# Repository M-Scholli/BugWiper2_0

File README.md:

## New ESP32-S3 Version

The new version of the BugWiper system is a complete redesign of the hardware and software to improve the performance, reliability and features of the system. The new design is based on the ESP32-S3 micro controller. The new design also includes a new motor with higher torque, a self locking gear and a motor encoder to measure the motor position and speed. The new design also includes a new software architecture that allows for more advanced features like programmable cable length, soft direction change of the motor at the wingtip, slow down the motor before reaching the fuselage and logging of all sensor data on an SD-card for later analysis and optimization of the system.

The BugWiper System cleans the wings in around 30 seconds as shown in this graph:

The documentation of the new version is still in progress, but you can already find some information about the hardware and software design in the following documents:
 [Documentation](./docs/doc.md)

 The user manual can be found here:
 [User Manual](./docs/user_manuel.md)

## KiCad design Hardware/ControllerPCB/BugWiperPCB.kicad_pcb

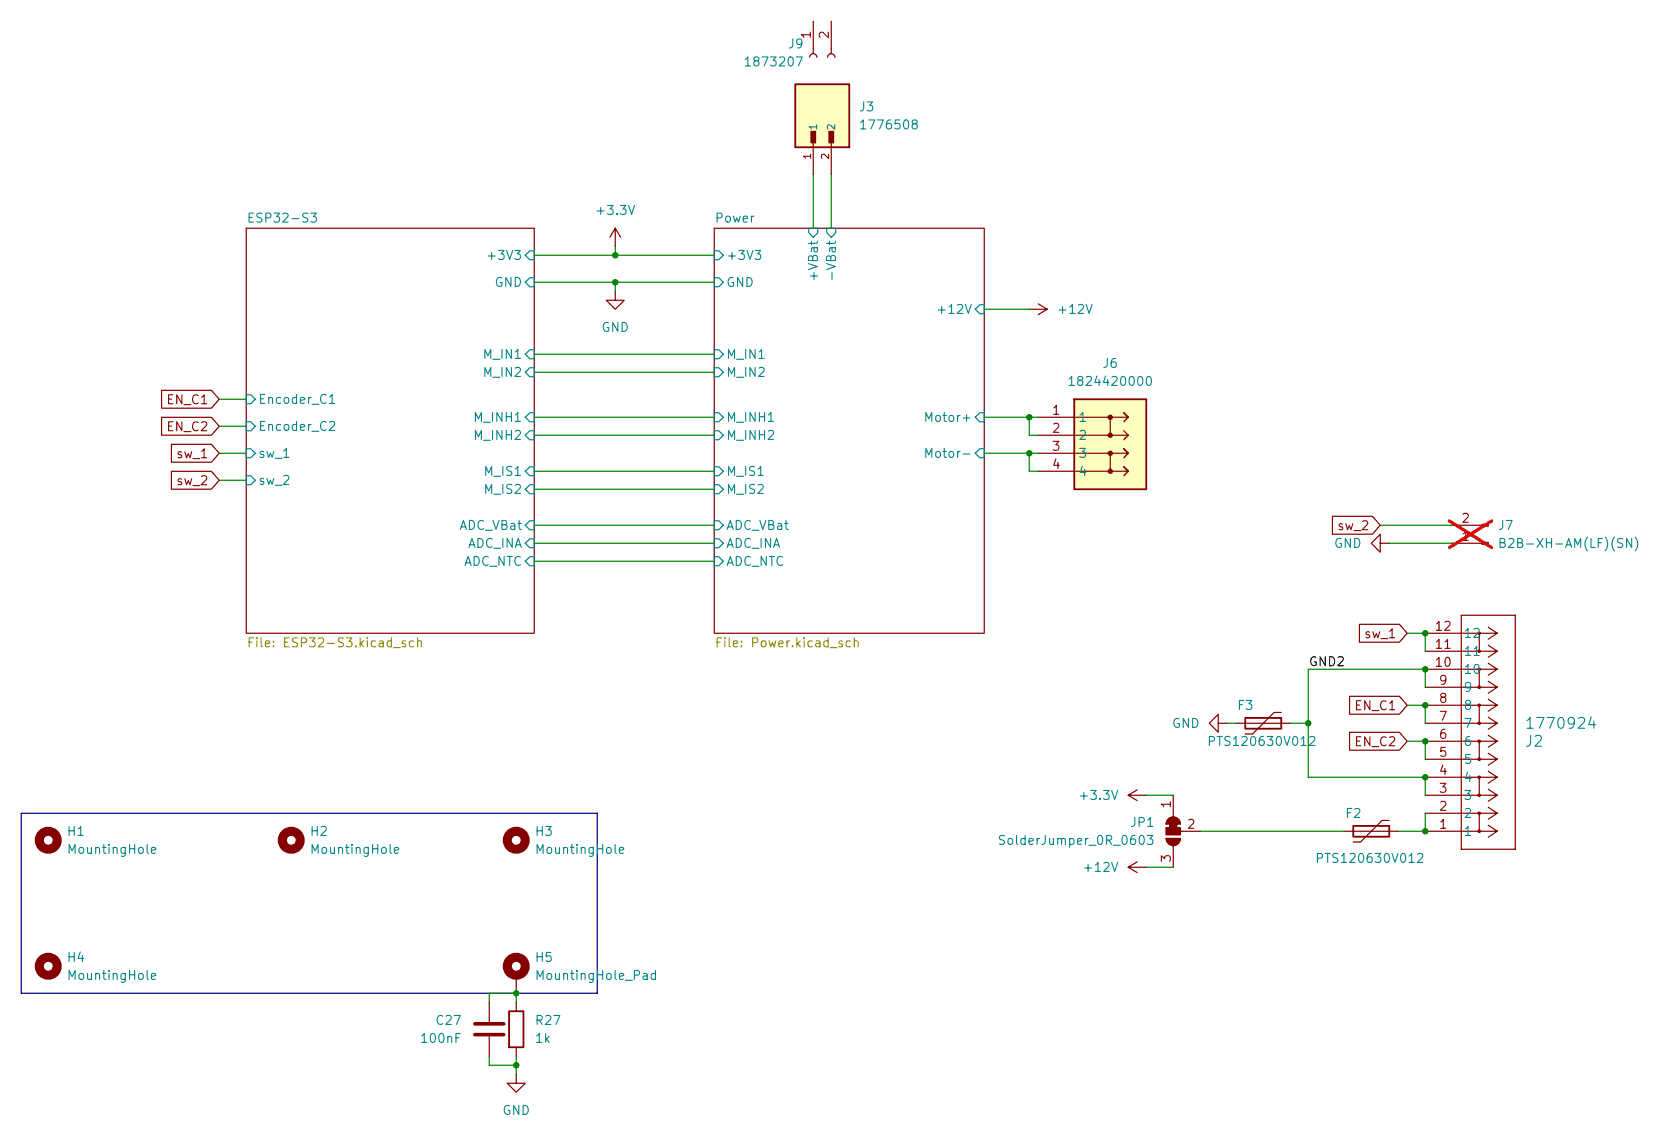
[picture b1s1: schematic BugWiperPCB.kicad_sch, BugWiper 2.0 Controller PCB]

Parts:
C27: 100nF; C_0603_1608Metric; Manufacturer_Part_Number CL10B104KB8NNNC; Mouser Part Number 187-CL10B104KB8NNNC
F2, F3: PTS120630V012; R_1206_3216Metric; Manufacturer_Part_Number PTS120630V012; Mouser Part Number 504-PTS120630V012
H1, H2, H3, H4: MountingHole; MountingHole_3.2mm_M3_DIN965_Pad
H5: MountingHole_Pad; MountingHole_3.2mm_M3_DIN965_Pad_TopBottom
J2: 1770924; CONN_1814537; Manufacturer_Part_Number 1770924; Mouser Part Number 651-1770924
J3: 1776508; PHOENIX_1776508; Manufacturer_Part_Number 1776508; Mouser Part Number 651-1776508
J6: 1824420000; SHDR4W80P700X350_2X2_770X1400X850P; Mouser Part Number 470-1824420000
J7: B2B-XH-AM(LF)(SN); JST_XH_B2B-XH-AM_1x02_P2.50mm_Vertical; Manufacturer_Part_Number B2B-XH-AM(LF)(SN); Mouser Part Number 306-B2B-XH-AMLFSNP; not fitted
J9: 1873207; Manufacturer_Part_Number 1873207; Mouser Part Number 651-1873207
JP1: SolderJumper_0R_0603; SolderJumper_R_SMD_0603; Manufacturer_Part_Number RC0603FR-070RL; Mouser Part Number 603-RC0603FR-070RL
R27: 1k; R_0603_1608Metric; Manufacturer_Part_Number RC0603FR-071KL; Mouser Part Number 603-RC0603FR-071KL

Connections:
+3.3V: JP1.1 (A); also elsewhere on the board
+12V: JP1.3 (B); also elsewhere on the board
/GND2: F3.1, J2.3, J2.4, J2.9, J2.10
/Power/+VBat: J3.1; also elsewhere on the board
/Power/Motor+: J6.1, J6.2; also elsewhere on the board
/Power/Motor-: J6.3, J6.4; also elsewhere on the board
EN_C1: J2.7, J2.8; also elsewhere on the board
EN_C2: J2.5, J2.6; also elsewhere on the board
GND: C27.2, F3.2, J3.2, J7.1, R27.2; also elsewhere on the board
unnamed: C27.1, H5.1, R27.1
unnamed: F2.1, J2.1, J2.2
unnamed: F2.2, JP1.2 (C)
sw_1: J2.11, J2.12; also elsewhere on the board
sw_2: J7.2; also elsewhere on the board

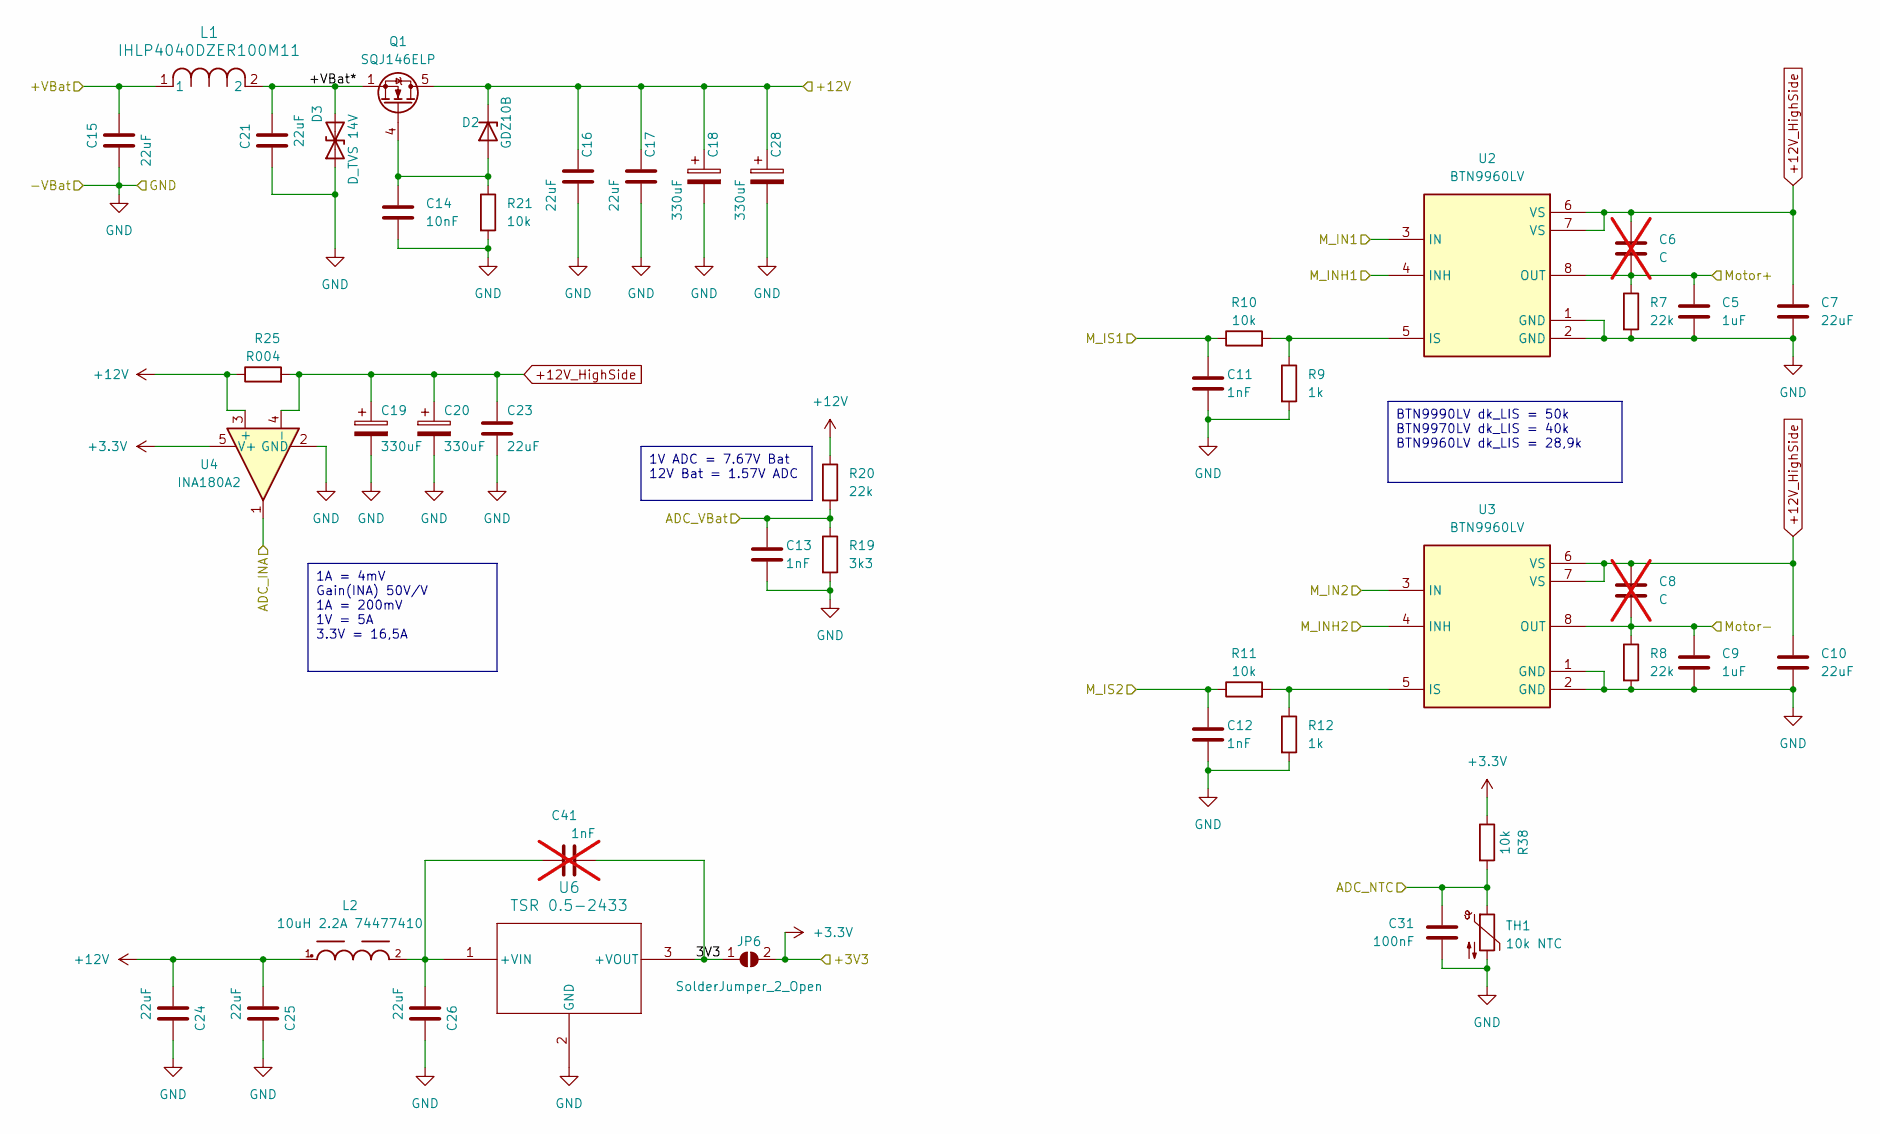
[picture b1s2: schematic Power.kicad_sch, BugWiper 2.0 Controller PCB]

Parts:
C5, C9: 1uF; C_0805_2012Metric; Manufacturer_Part_Number CL21B105MBFNNNE; Mouser Part Number 187-CL21B105MBFNNNE
C6, C8: C; C_0603_1608Metric; not fitted
C7, C10, C24, C25, C26: 22uF; C_1206_3216Metric; Manufacturer_Part_Number CL31A226KAHNNNE; Mouser Part Number 187-CL31A226KAHNNNE
C11, C12, C13: 1nF; C_0603_1608Metric; Manufacturer_Part_Number KAM15AR71H102KM; Mouser Part Number 581-KAM15AR71H102KM
C14: 10nF; C_0603_1608Metric; Manufacturer_Part_Number CL10B103KB8NFNC; Mouser Part Number 187-CL10B103KB8NFNC
C15, C16, C17, C21, C23: 22uF; C_1210_3225Metric; Manufacturer_Part_Number CL31A226KAHNNNE; Mouser Part Number 187-CL31A226KAHNNNE
C18, C19, C20, C28: 330uF; CP_Elec_8x10.5; Manufacturer_Part_Number UWT1E331MNL1GS; Mouser Part Number 647-UWT1E331MNL1S
C31: 100nF; C_0603_1608Metric; Manufacturer_Part_Number CL10B104KB8NNNC; Mouser Part Number 187-CL10B104KB8NNNC
C41: 1nF; C_0805_2012Metric_Pad1.18x1.45mm_HandSolder; not fitted
D2: GDZ10B; D_SOD-323_HandSoldering; Manufacturer_Part_Number GDZ10B-E3-08; Mouser Part Number 78-GDZ10B-E3-08
D3: D_TVS 14V; D_SMB; Manufacturer_Part_Number SMBJ14CA-13-F; Mouser Part Number 621-SMBJ14CA-13-F
JP6: SolderJumper_2_Open; SolderJumper-2_P1.3mm_Open_TrianglePad1.0x1.5mm
L1: IHLP4040DZER100M11; IND_IHLP-4040DZ_VIS; Manufacturer_Part_Number IHLP4040DZER100M11; Mouser Part Number 70-IHLP4040DZER100M1
L2: 10uH 2.2A 74477410; WE-PD2_5848; Manufacturer_Part_Number 74477410; Mouser Part Number 710-74477410
Q1: SQJ146ELP; PowerPAK_SO-8L_3_VIS; Manufacturer_Part_Number SQJ146ELP-T1_GE3; Mouser Part Number 78-SQJ146ELP-T1_GE3
R7, R8, R20: 22k; R_0603_1608Metric; Manufacturer_Part_Number AC0603FR-1022KL; Mouser Part Number 603-AC0603FR-1022KL
R9, R12: 1k; R_0603_1608Metric; Manufacturer_Part_Number RC0603FR-071KL; Mouser Part Number 603-RC0603FR-071KL
R10, R11, R21, R38: 10k; R_0603_1608Metric; Manufacturer_Part_Number RC0603FR-1010KL; Mouser Part Number 603-RC0603FR-1010KL
R19: 3k3; R_0603_1608Metric; Manufacturer_Part_Number CR0603-FX-3301ELF; Mouser Part Number 652-CR0603-FX3301ELF
R25: R004; R_1210_3225Metric; Manufacturer_Part_Number LRMAM1206-R004FT5; Mouser Part Number 756-LRMAM1206R004FT5
TH1: 10k NTC; R_0603_1608Metric; Manufacturer_Part_Number NCU18XH103E60RB; Mouser Part Number 81-NCU18XH103E60RB
U2, U3: BTN9960LV; IFX-PG-HSOF-7-1-V; Manufacturer_Part_Number BTN9960LVAUMA1; Mouser Part Number 726-BTN9960LVAUMA1
U4: INA180A2; SOT-23-5; Manufacturer_Part_Number INA180A2IDBVT; Mouser Part Number 595-INA180A2IDBVT
U6: TSR 0.5-2433; TSR0P5_TRP; Manufacturer_Part_Number R-78E3.3-0.5; Mouser Part Number 919-R-78E3.3-0.5

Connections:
+3.3V: JP6.2 (B), R38.1, U4.5 (V+); also elsewhere on the board
+12V: C16.1, C17.1, C18.1, C24.2, C25.2, C28.1, D2.1 (K), L2.1, Q1.5 (D), R20.1, R25.1, U4.3 (+); also elsewhere on the board
+12V_HighSide: C6.1, C7.1, C8.1, C10.1, C19.1, C20.1, C23.1, R25.2, U2.6 (VS), U2.7 (VS), U3.6 (VS), U3.7 (VS), U4.4 (-)
/ESP32-S3/ADC_INA: U4.1; also elsewhere on the board
/ESP32-S3/ADC_NTC: C31.1, R38.2, TH1.1; also elsewhere on the board
/ESP32-S3/ADC_VBat: C13.1, R19.1, R20.2; also elsewhere on the board
/ESP32-S3/M_IN1: U2.3 (IN); also elsewhere on the board
/ESP32-S3/M_IN2: U3.3 (IN); also elsewhere on the board
/ESP32-S3/M_INH1: U2.4 (INH); also elsewhere on the board
/ESP32-S3/M_INH2: U3.4 (INH); also elsewhere on the board
/ESP32-S3/M_IS1: C11.1, R10.1; also elsewhere on the board
/ESP32-S3/M_IS2: C12.1, R11.1; also elsewhere on the board
/Power/3V3: C41.2, JP6.1 (A), U6.3 (+VOUT)
/Power/+VBat: C15.1, L1.1; also elsewhere on the board
/Power/+VBat*: C21.2, D3.2 (A2), L1.2, Q1.1 (S), Q1.2 (S), Q1.3 (S)
/Power/Motor+: C5.1, C6.2, R7.1, U2.8 (OUT); also elsewhere on the board
/Power/Motor-: C8.2, C9.1, R8.1, U3.8 (OUT); also elsewhere on the board
GND: C5.2, C7.2, C9.2, C10.2, C11.2, C12.2, C13.2, C14.2, C15.2, C16.2, C17.2, C18.2, C19.2, C20.2, C21.1, C23.2, C24.1, C25.1, C26.1, C28.2, C31.2, D3.1 (A1), R7.2, R8.2, R9.2, R12.2, R19.2, R21.2, TH1.2, U2.1 (GND), U2.2 (GND), U3.1 (GND), U3.2 (GND), U4.2 (GND), U6.2 (GND); also elsewhere on the board
unnamed: C14.1, D2.2 (A), Q1.4 (G), R21.1
unnamed: R9.1, R10.2, U2.5 (IS)
unnamed: R11.2, R12.1, U3.5 (IS)
unnamed: C26.2, C41.1, L2.2, U6.1 (+VIN)

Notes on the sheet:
1A = 4mV Gain(INA) 50V/V 1A = 200mV 1V = 5A 3.3V = 16,5A
1V ADC = 7.67V Bat 12V Bat = 1.57V ADC
BTN9990LV dk_LIS = 50k BTN9970LV dk_LIS = 40k BTN9960LV dk_LIS = 28,9k

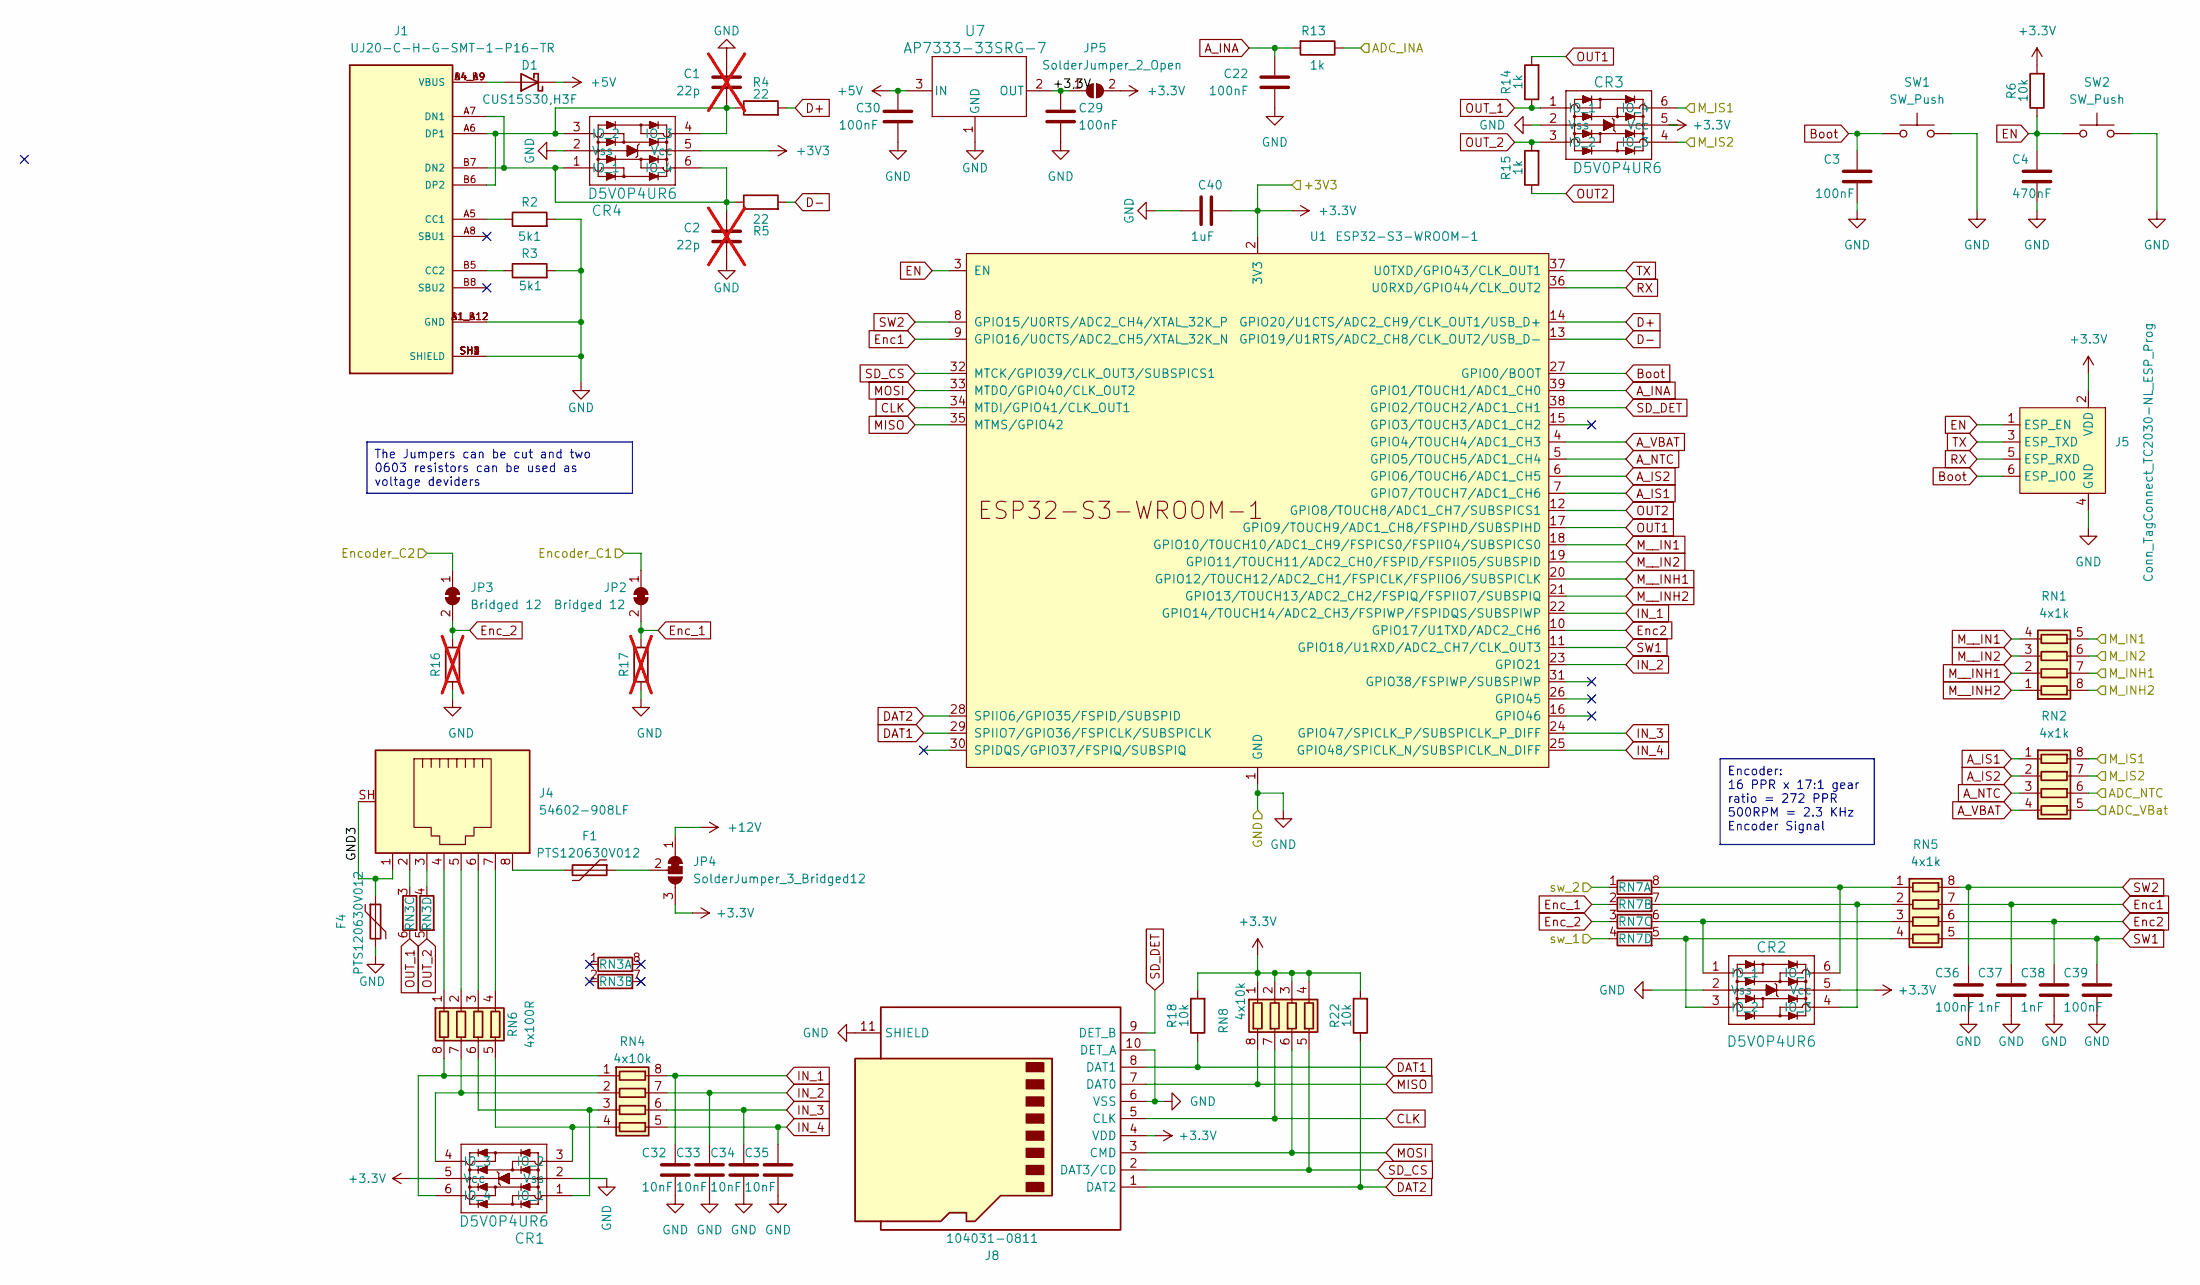
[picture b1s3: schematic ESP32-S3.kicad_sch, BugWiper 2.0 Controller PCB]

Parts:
C1, C2: 22p; C_0603_1608Metric; not fitted
C3, C22, C29, C30, C39: 100nF; C_0603_1608Metric; Manufacturer_Part_Number CL10B104KB8NNNC; Mouser Part Number 187-CL10B104KB8NNNC
C4: 470nF; C_0603_1608Metric; Manufacturer_Part_Number CL10B474KA8NFNC; Mouser Part Number 187-CL10B474KA8NFNC
C32, C33, C34, C35: 10nF; C_0603_1608Metric; Manufacturer_Part_Number CL10B103KB8NFNC; Mouser Part Number 187-CL10B103KB8NFNC
C36: 100nF; C_0603_1608Metric; Manufacturer_Part_Number CL10B103KB8NFNC; Mouser Part Number 187-CL10B103KB8NFNC
C37: 1nF; C_0603_1608Metric; Manufacturer_Part_Number CL10B103KB8NFNC; Mouser Part Number 187-CL10B103KB8NFNC
C38: 1nF; C_0603_1608Metric; Manufacturer_Part_Number CL10B104KB8NNNC; Mouser Part Number 187-CL10B104KB8NNNC
C40: 1uF; C_0805_2012Metric; Manufacturer_Part_Number CL21B105MBFNNNE; Mouser Part Number 187-CL21B105MBFNNNE
CR1, CR2, CR3, CR4: D5V0P4UR6; SOT26_DIO; Manufacturer_Part_Number D5V0P4UR6SO-7; Mouser Part Number 621-D5V0P4UR6SO-7
D1: CUS15S30,H3F; D_SOD-323_HandSoldering; Manufacturer_Part_Number CUS15S30,H3F; Mouser Part Number 757-CUS15S30H3F
F1, F4: PTS120630V012; R_1206_3216Metric; Manufacturer_Part_Number PTS120630V012; Mouser Part Number 504-PTS120630V012
J1: UJ20-C-H-G-SMT-1-P16-TR; SAMESKY_UJ20-C-H-G-SMT-1-P16-TR; Manufacturer_Part_Number UJ20-C-H-G-SMT-1-P16-TR; Mouser Part Number 179-UJ20CHGSMT1P16TR
J4: 54602-908LF; CONN8_2-908LF_AMP; Manufacturer_Part_Number 54602-908LF; Mouser Part Number 649-54602-908LF
J5: Conn_TagConnect_TC2030-NL_ESP_Prog; Tag-Connect_TC2030-IDC-NL_2x03_P1.27mm_Vertical; Mouser Price/Stock 0€
J8: 104031-0811; microSD_HC_Molex_104031-0811; Manufacturer_Part_Number 104031-0811; Mouser Part Number 538-104031-0811
JP2, JP3: Bridged 12; SolderJumper_2P_R_SMD_0603_Bridged
JP4: SolderJumper_3_Bridged12; SolderJumper_3P_R_SMD_0603_Bridged_12
JP5: SolderJumper_2_Open; SolderJumper-2_P1.3mm_Open_TrianglePad1.0x1.5mm
R2, R3: 5k1; R_0603_1608Metric; Manufacturer_Part_Number RC0603FR-105K1L; Mouser Part Number 603-RC0603FR-105K1L
R4, R5: 22; R_0603_1608Metric; Manufacturer_Part_Number CR0603-FX-22R0ELF; Mouser Part Number 652-CR0603FX-22R0ELF
R6, R18, R22: 10k; R_0603_1608Metric; Manufacturer_Part_Number RC0603FR-1010KL; Mouser Part Number 603-RC0603FR-1010KL
R13, R14, R15: 1k; R_0603_1608Metric; Manufacturer_Part_Number RC0603FR-071KL; Mouser Part Number 603-RC0603FR-071KL
R16, R17: R_0603_1608Metric; not fitted
RN1, RN2, RN5: 4x1k; RESCAV80P320X155X60-8N; Manufacturer_Part_Number CAY16-1001F4LF; Mouser Part Number 652-CAY16-1001F4LF
RN3, RN6, RN7: 4x100R; RESCAV80P320X155X60-8N; Manufacturer_Part_Number CAT16A-1000F4LF; Mouser Part Number 652-CAT16A-1000F4LF
RN4, RN8: 4x10k; RESCAV80P320X155X60-8N; Manufacturer_Part_Number CAT16A-1002F4LF; Mouser Part Number 652-CAT16A-1002F4LF
SW1, SW2: SW_Push; EVQ9P701P; Manufacturer_Part_Number EVQ-P3401P; Mouser Part Number 667-EVQP3401P
U1: ESP32-S3-WROOM-1; Manufacturer_Part_Number ESP32-S3-WROOM-1-N16R8; Mouser Part Number 356-ESP32S3WRM1N16R8
U7: AP7333-33SRG-7; SOT23R_DIO; Manufacturer_Part_Number AP7333-33SRG-7; Mouser Part Number 621-AP7333-33SRG-7

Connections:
+3.3V: C40.2, CR1.5 (Vcc), CR2.5 (Vcc), CR3.5 (Vcc), CR4.5 (Vcc), J5.2 (VDD), J8.4 (VDD), JP4.3 (B), JP5.2 (B), R6.2, R18.2, R22.2, RN8.1 (R1.1), RN8.2 (R2.1), RN8.3 (R3.1), RN8.4 (R4.1), U1.2 (3V3); also elsewhere on the board
+5V: C30.1, D1.1 (K), U7.3 (IN)
+12V: JP4.1 (A); also elsewhere on the board
/ESP32-S3/+3,3V: C29.1, JP5.1 (A), U7.2 (OUT)
/ESP32-S3/ADC_INA: R13.1; also elsewhere on the board
/ESP32-S3/ADC_NTC: RN2.6 (R3.2); also elsewhere on the board
/ESP32-S3/ADC_VBat: RN2.5 (R4.2); also elsewhere on the board
/ESP32-S3/GND3: F4.1, J4.1, J4.SH
/ESP32-S3/M_IN1: RN1.5 (R4.2); also elsewhere on the board
/ESP32-S3/M_IN2: RN1.6 (R3.2); also elsewhere on the board
/ESP32-S3/M_INH1: RN1.7 (R2.2); also elsewhere on the board
/ESP32-S3/M_INH2: RN1.8 (R1.2); also elsewhere on the board
/ESP32-S3/M_IS1: CR3.6 (IO_4), RN2.8 (R1.2); also elsewhere on the board
/ESP32-S3/M_IS2: CR3.4 (IO_3), RN2.7 (R2.2); also elsewhere on the board
A_INA: C22.1, R13.2, U1.39 (GPIO1/TOUCH1/ADC1_CH0)
A_IS1: RN2.1 (R1.1), U1.7 (GPIO7/TOUCH7/ADC1_CH6)
A_IS2: RN2.2 (R2.1), U1.6 (GPIO6/TOUCH6/ADC1_CH5)
A_NTC: RN2.3 (R3.1), U1.5 (GPIO5/TOUCH5/ADC1_CH4)
A_VBAT: RN2.4 (R4.1), U1.4 (GPIO4/TOUCH4/ADC1_CH3)
Boot: C3.1, J5.6 (ESP_IO0), SW1.1, U1.27 (GPIO0/BOOT)
CLK: J8.5 (CLK), RN8.7 (R2.2), U1.34 (MTDI/GPIO41/CLK_OUT1)
D+: R4.2, U1.14 (GPIO20/U1CTS/ADC2_CH9/CLK_OUT1/USB_D+)
D-: R5.2, U1.13 (GPIO19/U1RTS/ADC2_CH8/CLK_OUT2/USB_D-)
DAT1: J8.8 (DAT1), R18.1, U1.29 (SPIIO7/GPIO36/FSPICLK/SUBSPICLK)
DAT2: J8.1 (DAT2), R22.1, U1.28 (SPIIO6/GPIO35/FSPID/SUBSPID)
EN: C4.1, J5.1 (ESP_EN), R6.1, SW2.1, U1.3 (EN)
EN_C1: JP2.1 (A); also elsewhere on the board
EN_C2: JP3.1 (A); also elsewhere on the board
Enc1: C37.1, RN5.7 (R2.2), U1.9 (GPIO16/U0CTS/ADC2_CH5/XTAL_32K_N)
Enc2: C38.1, RN5.6 (R3.2), U1.10 (GPIO17/U1TXD/ADC2_CH6)
Enc_1: JP2.2 (A), R17.2, RN7.2 (R2.1)
Enc_2: JP3.2 (A), R16.2, RN7.3 (R3.1)
GND: C1.1, C2.2, C3.2, C4.2, C22.2, C29.2, C30.2, C32.2, C33.2, C34.2, C35.2, C36.2, C37.2, C38.2, C39.2, C40.1, CR1.2 (Vss), CR2.2 (Vss), CR3.2 (Vss), CR4.2 (Vss), F4.2, J1.A1_B12 (GND), J1.B1_A12 (GND), J1.SH1 (SHIELD), J1.SH2 (SHIELD), J1.SH3 (SHIELD), J1.SH4 (SHIELD), J5.4 (GND), J8.6 (VSS), J8.10 (DET_A), J8.11 (SHIELD), R2.2, R3.2, R16.1, R17.1, SW1.2, SW2.2, U1.1 (GND), U1.40 (GND), U1.41 (GND), U7.1 (GND); also elsewhere on the board
IN_1: C32.1, RN4.8 (R1.2), U1.22 (GPIO14/TOUCH14/ADC2_CH3/FSPIWP/FSPIDQS/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)
IN_2: C33.1, RN4.7 (R2.2), U1.23 (GPIO21)
IN_3: C34.1, RN4.6 (R3.2), U1.24 (GPIO47/SPICLK_P/SUBSPICLK_P_DIFF)
IN_4: C35.1, RN4.5 (R4.2), U1.25 (GPIO48/SPICLK_N/SUBSPICLK_N_DIFF)
MISO: J8.7 (DAT0), RN8.8 (R1.2), U1.35 (MTMS/GPIO42)
MOSI: J8.3 (CMD), RN8.6 (R3.2), U1.33 (MTDO/GPIO40/CLK_OUT2)
M__IN1: RN1.4 (R4.1), U1.18 (GPIO10/TOUCH10/ADC1_CH9/FSPICS0/FSPIIO4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)
M__IN2: RN1.3 (R3.1), U1.19 (GPIO11/TOUCH11/ADC2_CH0/FSPID/FSPIIO5/S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)
M__INH1: RN1.2 (R2.1), U1.20 (GPIO12/TOUCH12/ADC2_CH1/FSPICLK/FSPIIO6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)
M__INH2: RN1.1 (R1.1), U1.21 (GPIO13/TOUCH13/ADC2_CH2/FSPIQ/FSPIIO7/S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)
unnamed: CR1.1 (IO_1), RN4.3 (R3.1), RN6.6 (R3.2)
unnamed: CR1.3 (IO_2), RN4.4 (R4.1), RN6.5 (R4.2)
unnamed: CR1.4 (IO_3), RN4.2 (R2.1), RN6.7 (R2.2)
unnamed: CR1.6 (IO_4), RN4.1 (R1.1), RN6.8 (R1.2)
unnamed: CR2.1 (IO_1), RN5.3 (R3.1), RN7.6 (R3.2)
unnamed: CR2.3 (IO_2), RN5.4 (R4.1), RN7.5 (R4.2)
unnamed: CR2.4 (IO_3), RN5.2 (R2.1), RN7.7 (R2.2)
unnamed: CR2.6 (IO_4), RN5.1 (R1.1), RN7.8 (R1.2)
unnamed: C2.1, CR4.1 (IO_1), CR4.6 (IO_4), J1.A7 (DN1), J1.B7 (DN2), R5.1
unnamed: C1.2, CR4.3 (IO_2), CR4.4 (IO_3), J1.A6 (DP1), J1.B6 (DP2), R4.1
unnamed: D1.2 (A), J1.A4_B9 (VBUS), J1.B4_A9 (VBUS)
unnamed: F1.2, J4.8
unnamed: J1.A5 (CC1), R2.1
unnamed: J1.B5 (CC2), R3.1
unnamed: F1.1, JP4.2 (C)
unnamed: J4.2, RN3.3 (R3.1)
unnamed: J4.3, RN3.4 (R4.1)
unnamed: J4.4, RN6.1 (R1.1)
unnamed: J4.5, RN6.2 (R2.1)
unnamed: J4.6, RN6.3 (R3.1)
unnamed: J4.7, RN6.4 (R4.1)
OUT1: R14.2, U1.17 (GPIO9/TOUCH9/ADC1_CH8/FSPIHD/SUBSPIHD)
OUT2: R15.1, U1.12 (GPIO8/TOUCH8/ADC1_CH7/SUBSPICS1)
OUT_1: CR3.1 (IO_1), R14.1, RN3.6 (R3.2)
OUT_2: CR3.3 (IO_2), R15.2, RN3.5 (R4.2)
RX: J5.5 (ESP_RXD), U1.36 (U0RXD/GPIO44/CLK_OUT2)
SD_CS: J8.2 (DAT3/CD), RN8.5 (R4.2), U1.32 (MTCK/GPIO39/CLK_OUT3/SUBSPICS1)
SD_DET: J8.9 (DET_B), U1.38 (GPIO2/TOUCH2/ADC1_CH1)
SW1: C39.1, RN5.5 (R4.2), U1.11 (GPIO18/U1RXD/ADC2_CH7/CLK_OUT3)
SW2: C36.1, RN5.8 (R1.2), U1.8 (GPIO15/U0RTS/ADC2_CH4/XTAL_32K_P)
TX: J5.3 (ESP_TXD), U1.37 (U0TXD/GPIO43/CLK_OUT1)
sw_1: RN7.4 (R4.1); also elsewhere on the board
sw_2: RN7.1 (R1.1); also elsewhere on the board

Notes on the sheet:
Encoder: 16 PPR x 17:1 gear ratio = 272 PPR 500RPM = 2.3 KHz Encoder Signal
The Jumpers can be cut and two 0603 resistors can be used as voltage deviders

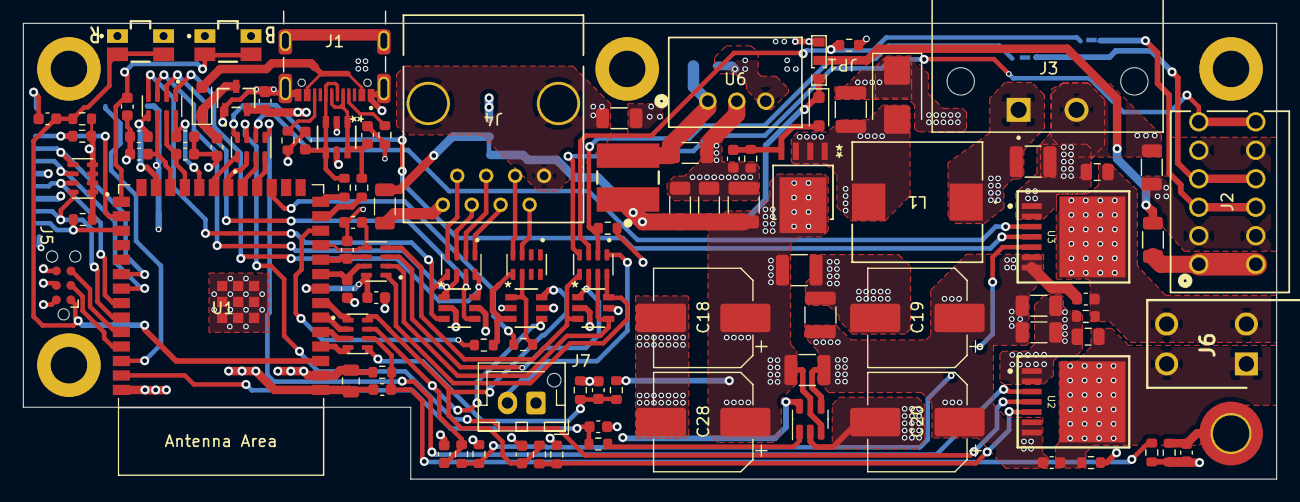
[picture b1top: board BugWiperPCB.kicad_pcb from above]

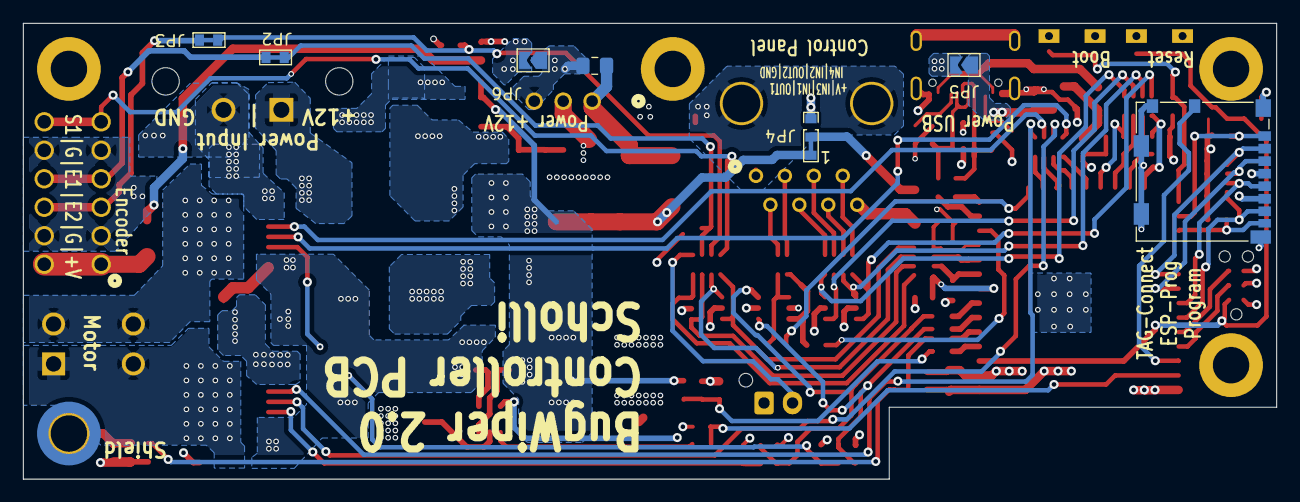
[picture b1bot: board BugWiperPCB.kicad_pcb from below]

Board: 4 copper layers, 110.0 x 40.0 mm, 115 parts (7 on the bottom side), 90 nets.

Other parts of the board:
locked: MountingHole; MountingHole_3.2mm_M3_DIN965_Pad

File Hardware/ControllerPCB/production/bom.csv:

Designator,Footprint,Quantity,Value,LCSC Part #
"C10, C24, C25, C26, C7",1206,5,22uF 25V,
"C11, C12, C13",0603,3,1nF,
"C14, C32, C33, C34, C35, C36, C37",0603,7,10nF ,
"C15, C16, C17, C21, C23",1210,5,22uF 25V,
"C18, C19, C20, C28",CP_Elec_8x10.5,4,470uF 16V,
"C22, C27, C29, C3, C30, C31, C38, C39, C4",0603,9,100nF ,
"C40, C5, C9",0805,3,1uF 50V,
"CR1, CR2, CR3, CR4",SOT26_DIO,4,D5V0P4UR6SO-7,
D1,D_SOD-323_HandSoldering,1,"CUS15S30,H3F",
D2,D_SOD-323_HandSoldering,1,D_Zener 10V,
D3,D_SMB,1,D_TVS 15V,
"F1, F2, F3, F4",1206,4,100mA Polyfuse,
"H1, H2, H3, H4",MountingHole_3.2mm_M3_DIN965_Pad,4,MountingHole,
H5,MountingHole_3.2mm_M3_DIN965_Pad_TopBottom,1,MountingHole_Pad,
J1,SAMESKY_UJ20-C-H-G-SMT-1-P16-TR,1,UJ20-C-H-G-SMT-1-P16-TR,
J2,CONN_1814537,1,1770924,
J3,PHOENIX_1776508,1,Phoenix_1776508,
J4,CONN8_2-908LF_AMP,1,RJ45,
J6,SHDR4W80P700X350_2X2_770X1400X850P,1,1824420000,
J7,JST_XH_B2B-XH-AM_1x02_P2.50mm_Vertical,1,Conn_01x02_Pin,
J8,microSD_HC_Molex_104031-0811,1,Micro_SD_Card,
JP1,SolderJumper_R_SMD_0603,1,SolderJumper_3_Open,
"JP2, JP3",SolderJumper_2P_R_SMD_0603_Bridged,2,Bridged 12,
JP4,SolderJumper_3P_R_SMD_0603_Bridged_12,1,SolderJumper_3_Bridged12,
"JP5, JP6",SolderJumper-2_P1.3mm_Open_TrianglePad1.0x1.5mm,2,SolderJumper_2_Open,
L1,IND_IHLP-4040DZ_VIS,1,IHLP4040DZER100M1A,
L2,WE-PD2_5848,1,10µH 2.2A,
Q1,PowerPAK_SO-8L_3_VIS,1,SQJ146ELP-T1_GE3,
"R10, R11, R18, R21, R22, R38, R6",0603,7,10k,
"R12, R13, R14, R15, R27, R9",0603,6,1k,
R19,0603,1,3k3,
"R2, R3",0603,2,5k1,
R20,0603,1,22k,
R25,1210,1,R004,
"R4, R5",0603,2,22,
"RN1, RN2, RN5",RESCAV80P320X155X60-8N,3,1k x 4,
"RN3, RN6, RN7",RESCAV80P320X155X60-8N,3,100R x 4,
"RN4, RN8",RESCAV80P320X155X60-8N,2,10k x 4,
"S1, S2",SW_EVP-AT2L1B000,2,EVP-AT2L1B000,
TH1,0603,1,Thermistor_NTC,
U1,ESP32-S3-WROOM-1,1,ESP32-S3-WROOM-1,
"U2, U3",IFX-PG-HSOF-7-1-V,2,BTN9960LV,
U4,SOT-23-5,1,INA180A2,
U6,TSR0P5_TRP,1,TSR 0.5-2433,
U7,SOT23R_DIO,1,AP7333-33SRG-7,

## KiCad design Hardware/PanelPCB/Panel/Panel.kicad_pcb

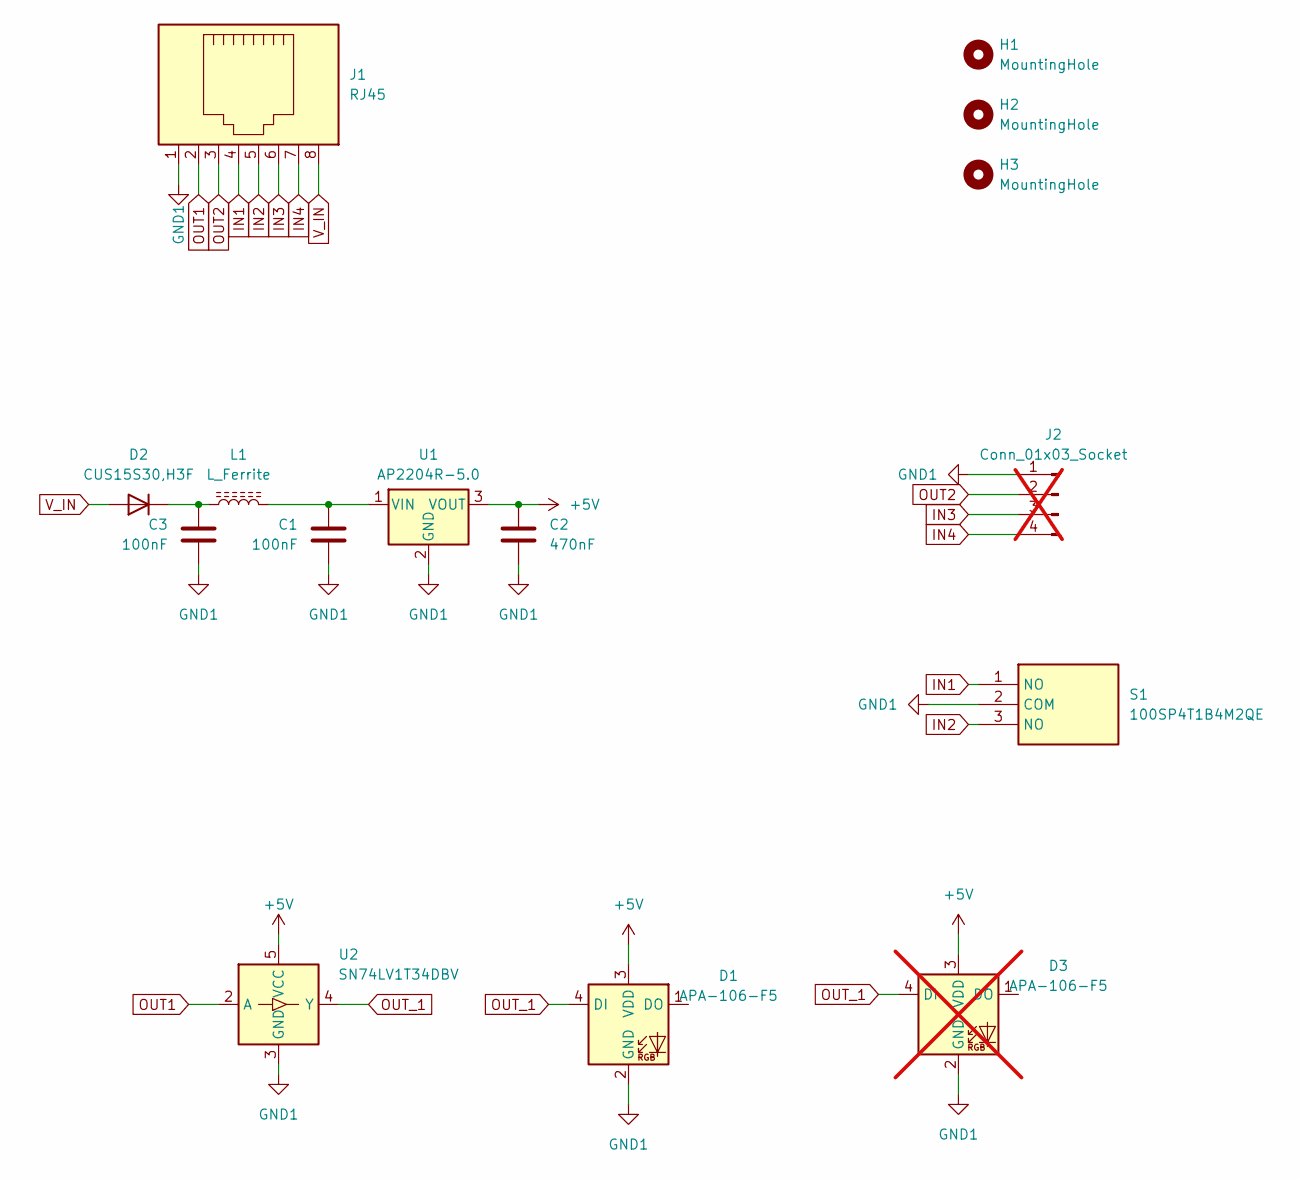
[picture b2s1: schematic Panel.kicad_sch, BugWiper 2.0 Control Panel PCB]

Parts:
C1, C3: 100nF; C_0603_1608Metric; Manufacturer_Part_Number CL10B104KB8NNNC; Mouser Part Number 187-CL10B104KB8NNNC
C2: 470nF; C_0603_1608Metric; Manufacturer_Part_Number CL10B474KA8NFNC; Mouser Part Number 187-CL10B474KA8NFNC
D1: APA-106-F5; LED_D5.0mm-4_RGB_Wide_Pins; Manufacturer_Part_Number APA-106-F5
D2: CUS15S30,H3F; D_SOD-323_HandSoldering; Manufacturer_Part_Number CUS15S30,H3F; Mouser Part Number 757-CUS15S30H3F
D3: APA-106-F5; LED_D5.0mm-4_RGB_Wide_Pins; Manufacturer_Part_Number APA-106-F5; not fitted
H1, H2, H3: MountingHole; MountingHole_2.7mm_M2.5_DIN965_Pad
J1: RJ45; MJ3415882; Manufacturer_Part_Number MJ3415-88-2; Mouser Part Number 640-MJ3415-88-2
J2: Conn_01x03_Socket; PinHeader_1x04_P2.54mm_Vertical; not fitted
L1: L_Ferrite; L_0805_2012Metric; Manufacturer_Part_Number ILBB0805ER151V; Mouser Part Number 70-ILBB0805ER151V
S1: 100SP4T1B4M2QE; Mouser Part Number 612-100SP4T1B4M2QE
U1: AP2204R-5.0; SOT-89-3; Manufacturer_Part_Number AP2204R-5.0TRG1; Mouser Part Number 621-AP2204R-5.0TRG1
U2: SN74LV1T34DBV; SOT-23-5; Manufacturer_Part_Number SN74LV1T34DBVR; Mouser Part Number 595-SN74LV1T34DBVR

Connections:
+5V: C2.1, D1.3 (VDD), D3.3 (VDD), U1.3 (VOUT), U2.5 (VCC)
GND1: C1.2, C2.2, C3.2, D1.2 (GND), D3.2 (GND), J1.1, J2.1, S1.2 (COM), U1.2 (GND), U2.3 (GND)
IN1: J1.4, S1.1 (NO)
IN2: J1.5, S1.3 (NO)
IN3: J1.6, J2.3
IN4: J1.7, J2.4
unnamed: C3.1, D2.1 (K), L1.1
unnamed: C1.1, L1.2, U1.1 (VIN)
OUT1: J1.2, U2.2 (A)
OUT2: J1.3, J2.2
OUT_1: D1.4 (DI), D3.4 (DI), U2.4 (Y)
V_IN: D2.2 (A), J1.8

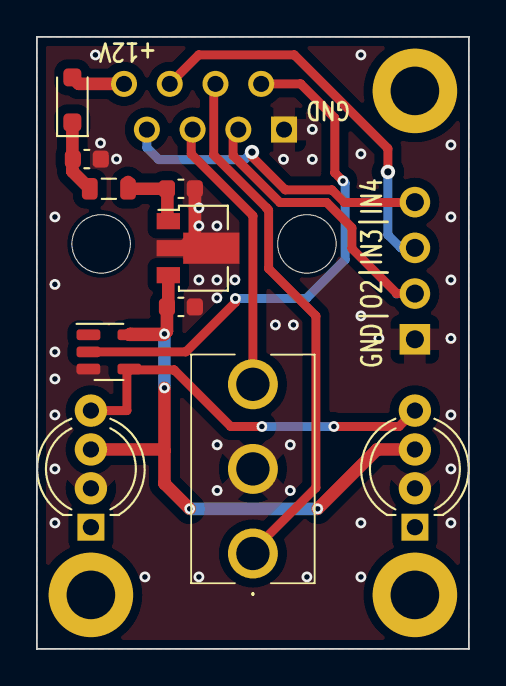
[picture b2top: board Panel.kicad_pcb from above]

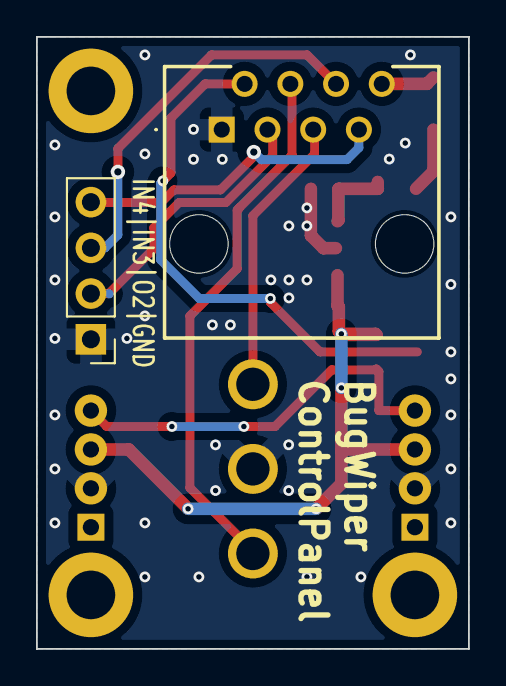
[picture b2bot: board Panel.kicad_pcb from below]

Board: 2 copper layers, 24.0 x 34.0 mm, 15 parts (2 on the bottom side), 12 nets.
